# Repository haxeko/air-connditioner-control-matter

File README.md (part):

# Bộ điều khiển máy lạnh IR – Matter Thermostat (ESP32-S3)

Firmware ESP-IDF thuần (không Arduino, không ESPHome, không Home Assistant/MQTT/RainMaker/cloud) cho
ESP32-S3 N16R8:

- xuất hiện trong Google Home, Apple Home, SmartThings, Alexa, Aqara Home, Home Assistant… dưới dạng
  **máy lạnh / Matter Thermostat** tên **`May lanh IR v1.7.0`** (Tắt/Làm lạnh, Sưởi/Khô/Quạt khi profile máy
  lạnh có các chế độ đó; tốc độ quạt và đảo gió qua cluster Fan Control);
- tự tạo **fabric riêng (Fabric B)** để ghép cảm biến nhiệt độ Matter đã có trong nhà bằng Multi-Admin,
  rồi **subscribe** trực tiếp nhiệt độ của cảm biến (kể cả cảm biến Thread qua Border Router sẵn có);
- điều khiển máy lạnh bằng hồng ngoại (RMT native của ESP-IDF): **bấm remote một lần để tự nhận diện giao
  thức** (thư viện IRremoteESP8266, hơn 80 giao thức máy lạnh) rồi firmware tự tạo mọi lệnh, hoặc **học từng
  lệnh từ remote gốc** cho máy không có trong thư viện;
- **vẫn dùng remote gốc được**: mắt thu luôn nghe, bấm remote thì trạng thái mới (bật/tắt, chế độ, nhiệt độ,
  quạt, đảo gió) hiện lên Apple Home/Google Home… và lệnh sau từ ứng dụng nối tiếp đúng trạng thái đó;
- **nhấn BOOT 2 lần** để vào **chế độ ghép Matter** (LED RGB nháy xanh dương): ứng dụng nhà tìm thấy
  thiết bị **qua Bluetooth** (và qua Wi-Fi nhà nếu ESP đã vào mạng), thêm bằng **mã QR hoặc mã 11 số**;
  ứng dụng tự gửi Wi-Fi nhà cho ESP qua Bluetooth;
- **nhấn BOOT 3 lần** để mở Wi-Fi cấu hình và trang web tiếng Việt tại `http://192.168.4.1`;
- **giữ BOOT 10 giây rồi thả** để rời khỏi mọi ứng dụng nhà (giữ Wi-Fi, cảm biến, profile); **giữ 20 giây** để
  đặt lại gốc; cả hai cũng làm được trên web;
- **cập nhật firmware ngay trên trang web** (tải file `.bin`), không cần dây nạp; firmware mới lỗi thì tự quay
  về bản cũ;
- **tự phục hồi và tự báo lỗi**: treo thì watchdog khởi động lại; lỗi nghiêm trọng để lại báo cáo (tác vụ, vị trí)
  đọc được trên trang Chẩn đoán;
- lưu mọi cấu hình vào flash: mất điện không phải thiết lập lại;
- mọi tên thiết bị phát ra đều có **hậu tố phiên bản firmware** (`v1.7.0`): tên Matter, tên Bluetooth
  `AC-XXXX-v1.7.0`, Wi-Fi cấu hình `AC-Matter-XXXX-v1.7.0` – nhìn tên là biết thiết bị đang chạy bản nào.

### Có gì mới trong v1.7.0

Sửa đồng bộ với **Apple Home** (báo lỗi: bấm remote gốc thì mắt nhận nhưng Apple Home không đổi; bật trên Apple
Home thì một lúc sau tự tắt). Apple Home hiển thị thiết bị loại *Room Air Conditioner* như một máy sưởi/làm mát
(HomeKit Heater/Cooler, theo trả lời của kỹ sư Apple trên diễn đàn nhà phát triển); trạng thái “đang chạy” và quạt
của loại này lấy từ các thuộc tính mà bản trước không báo đúng:

- **Trạng thái đang chạy** (`ThermostatRunningState`, mới): Làm lạnh/Khô → “đang làm lạnh”, Sưởi → “đang sưởi”,
  Quạt → “quạt chạy”, Tắt → không. Trước đây thuộc tính này không có, nên Apple Home có thể hiện ô máy lạnh là
  Tắt/Chờ dù máy đang chạy – cả khi bật từ Apple Home lẫn khi bật bằng remote gốc.
- **Quạt Tự động không còn báo tốc độ hiện tại 0 %**: khi máy chạy với quạt tự động, tốc độ hiện tại báo là mức
  giữa (ví dụ 2/3). Ứng dụng nhà coi quạt 0 % là quạt tắt, tức máy tắt.
- **Quạt không còn bật/tắt máy lạnh**: trước đây ghi “quạt Off”/0 % (thanh trượt về cuối, hoặc ứng dụng tự ghi lại
  một tốc độ nó không biết) **tắt máy lạnh**, và chọn tốc độ khi máy tắt thì **bật máy**. Nay bật/tắt chỉ đi qua
  On/Off và chế độ (`SystemMode`); quạt Off/0 % nghĩa là quạt tự động; chọn tốc độ lúc máy tắt được dùng ở lần bật
  sau. Đây là nguyên nhân khả dĩ của “bật lên một lúc thì tự tắt” khi ứng dụng gửi kèm lệnh quạt.
- Trang **Máy lạnh** có dòng mới **Ứng dụng nhà đang thấy**: đúng những gì thiết bị đang báo qua Matter (bật/tắt,
  chế độ, nhiệt độ đặt, đang làm lạnh, quạt) và ai đổi lần cuối (ứng dụng nhà, remote gốc, trang này). Bấm remote
  rồi xem dòng này: nếu nó đổi mà Apple Home không đổi thì phần còn lại nằm ở Apple Home/bộ trung tâm.

Về chế độ: Apple Home chỉ có **Tắt / Sưởi / Làm lạnh / Tự động** cho máy lạnh, và chỉ hiện chế độ mà thiết bị khai báo
được (máy chỉ làm lạnh → chỉ Tắt và Làm lạnh). **Khô và Quạt không có trong Apple Home** (HomeKit không có hai chế độ
này); **Tự động** của Matter đòi máy có cả Sưởi, và với loại Room Air Conditioner thì Apple Home đang gửi Làm lạnh
khi chọn Tự động (lỗi Apple đã xác nhận). Khô/Quạt/Tự động vẫn dùng được bằng remote gốc, trang web, và ứng dụng hỗ
trợ (Home Assistant, SmartThings…). Xem [mục 10](#10-giới-hạn-đã-biết).

### Có gì mới trong v1.6.0

Bản rà soát và tối ưu (firmware và [mạch in v1.4](hardware/ac-ir-s3/README.md)). Cách điều khiển máy lạnh không
đổi; thiết bị tự phục hồi tốt hơn và nói được vì sao nó khởi động lại.

Độ tin cậy và chẩn đoán:

- **Treo thì tự khởi động lại**: một tác vụ chiếm CPU quá 15 giây làm thiết bị panic và khởi động lại (trước đây
  watchdog chỉ in cảnh báo ra cổng serial, thiết bị vẫn treo).
- **Báo cáo sự cố**: khi firmware lỗi nghiêm trọng (exception, abort, watchdog), thiết bị lưu core dump vào phân
  vùng `coredump` trước khi khởi động lại. Tab **Chẩn đoán → Sự cố khởi động lại** (và lệnh console `diag`) hiện
  tác vụ gây lỗi, vị trí và chuỗi địa chỉ gọi hàm – chỉ là địa chỉ trong chương trình, không có nội dung bộ nhớ.
  `python tools/decode_backtrace.py <địa chỉ…>` đổi các địa chỉ đó thành tên hàm bằng file
  `ac_matter_ir_vX.Y.Z_symbols.txt.gz` của đúng phiên bản (không cần ESP-IDF). Phân vùng này chỉ có trên bo nạp file `full` từ
  v1.6.0, hoặc nạp thêm file bảng phân vùng (xem [firmware/README.md](firmware/README.md)); bo chỉ cập nhật file
  app thì chạy bình thường, chỉ là không lưu báo cáo.
- **Ngăn xếp của từng tác vụ** (số byte còn trống ít nhất từ lúc khởi động) trên trang Chẩn đoán và lệnh `diag`:
  thấy ngay tác vụ nào sát giới hạn khi chạy trên bo thật.
- **Identify**: ứng dụng nhà bấm “nhận diện thiết bị” thì LED nháy **trắng**.

Sửa lỗi (các mục còn lại của lần rà soát trước):

- Phát IR bị quá hạn: kênh phát được dừng trước khi bộ đệm lệnh bị giải phóng (trước đây ngắt phát có thể còn đọc
  vùng nhớ đã trả lại).
- Vừa phát một lệnh, người dùng bấm remote gốc đổi trạng thái, rồi ứng dụng nhà lại yêu cầu đúng lệnh vừa phát
  (trong 1,5 giây): lệnh không còn bị coi là trùng và bỏ qua.
- Khởi động lại từ trang web (kể cả sau khi cập nhật firmware): lệnh IR đang chờ được phát nốt và trạng thái máy
  lạnh được lưu trước khi khởi động lại (trước đây có thể mất thay đổi của 10 giây cuối).
- Thuộc tính `ControlSequenceOfOperation` không còn ghi được sang kiểu mà máy lạnh không có (ví dụ “có sưởi” với
  profile chỉ làm lạnh); giá trị cũ sai được sửa lúc khởi động.
- Cổng cấu hình khởi tạo lỗi không còn làm thiết bị khởi động lại liên tục: thermostat và IR vẫn chạy.

Cấu hình:

- Tắt hẳn bộ mã ghép thử nghiệm của SDK (`CONFIG_ENABLE_TEST_SETUP_PARAMS=n`): không còn đường nào quay về
  passcode `20202021` (thiết bị vốn dùng mã riêng từng máy).
- Chọn GPIO không dùng được trên N16R8 (flash/PSRAM 26–37, UART0 43/44, chân strapping cho ngõ ra IR, hai chức
  năng trùng chân) bị từ chối **lúc build** thay vì hỏng lúc chạy.

### Có gì mới trong v1.5.0

Tính năng mới:

- **Cập nhật firmware qua web** (tab Chẩn đoán → *Cập nhật firmware*): chọn file `ac_matter_ir_vX.Y.Z_app_0x40000.bin`,
  thiết bị ghi vào khe OTA còn lại, kiểm tra nội dung rồi khởi động lại. Mọi dữ liệu được giữ. Firmware mới chạy
  thử 60 giây; nếu thiết bị reset trong thời gian đó, bootloader quay về bản cũ. Chi tiết ở [mục 7.5](#75-cập-nhật-firmware-và-đặt-lại).
- **Rời khỏi ứng dụng nhà ngay trên thiết bị**: gỡ từng hệ sinh thái hoặc tất cả (tab Nhà thông minh), hoặc
  **giữ BOOT 10 giây rồi thả** (LED nháy đỏ nhanh). Dùng khi hub đã mất hoặc đã xóa thiết bị lúc ESP mất mạng.
  Wi-Fi, cảm biến, profile IR và cài đặt được giữ; chế độ ghép tự bật lại.
- **Đặt lại gốc**: tab Chẩn đoán → *Đặt lại gốc*, hoặc **giữ BOOT 20 giây** (LED đỏ sáng liên tục). Xóa Wi-Fi, mọi
  fabric, cảm biến và cài đặt; giữ mã ghép Matter (tem QR đã in vẫn dùng được) và profile IR.

Sửa lỗi (tìm thấy khi rà soát mã nguồn):

- **Không còn tự phát lệnh IR**: trước đây, sau khi lưu/khóa/chọn profile (hoặc sau khi NVS bị xóa), thiết bị tự
  phát trạng thái thermostat trong vòng 30 giây – thường là lệnh *Tắt* – dù không ai yêu cầu. Nay khi chưa biết
  máy lạnh đang ở trạng thái nào, thiết bị coi như đã khớp và chỉ phát khi có thay đổi thật. Lúc khởi động cũng
  không bao giờ phát (trừ khi bật *Gửi lại trạng thái cuối sau khi mất điện*).
- **Bật máy kèm đổi chế độ** từ ứng dụng nhà (lệnh On và ghi SystemMode đi sát nhau) không còn có thể bị ghi đè
  bằng chế độ của lần bật trước.
- Ứng dụng nhà ghi lại đúng giá trị đang có (cảnh/tự động hóa lặp lại) không còn làm lùi chu kỳ bù theo cảm biến.
- Đổi Wi-Fi mà mất điện giữa lúc thử kết nối: lần khởi động sau tự quay về mạng cũ.
- Bộ thu IR: loại bỏ một tình huống tranh chấp hiếm giữa ngắt thu và việc dừng bộ thu (có thể gây khởi động lại).

### Có gì mới trong v1.4.0

- **Đồng bộ khi bấm remote gốc**: v1.3.0 chỉ dùng mắt thu lúc học/nhận diện, nên bấm remote thì máy lạnh đổi
  nhưng ESP và ứng dụng nhà không biết. Từ v1.4.0, khi profile đang dùng **đã khóa**, mắt thu nghe liên tục:
  lệnh của remote được giải mã theo profile (profile thư viện: đúng giao thức, ví dụ `SHARP_AC`; profile học
  thủ công: so với các lệnh đã học), rồi trạng thái mới được hiển thị trong ứng dụng nhà (SystemMode,
  nhiệt độ đặt, On/Off, quạt, đảo gió) **mà không phát lại IR**. Lệnh tiếp theo từ ứng dụng dùng trạng thái
  đó làm trạng thái trước (quan trọng với giao thức “đảo trạng thái” như Sharp). Chi tiết ở
  [mục 7.4](#74-ir), tắt được ở tab Thuật toán (*Đồng bộ khi bấm remote gốc*).
- Trang Máy lạnh có dòng **Remote gốc**: trạng thái remote đặt lần cuối, hoặc lý do lệnh cuối bị bỏ qua (ví dụ
  `giao thức NEC, profile dùng SHARP_AC` khi bấm remote TV). Lệnh `status` có dòng `Remote  :`.
- Thêm kiểm tra trên máy tính: chuỗi bấm remote Sharp (bật, đổi nhiệt độ, quạt, Sưởi, Khô, Tắt) qua mô phỏng
  mắt thu được đọc lại đúng trạng thái; trạng thái remote → trạng thái thermostat; sau khi bấm remote thuật
  toán không phát lại lệnh (cả chế độ Theo cảm biến ngoài).

### Có gì mới trong v1.3.0

- **Nhận diện remote tự động**: tab Máy lạnh → *Bắt đầu nhận diện* → bấm một nút trên remote. Firmware giải
  mã tín hiệu bằng thư viện **IRremoteESP8266 v2.9.0** (ESP-IDF thuần, không Arduino; `components/irremote_esp8266`),
  cho biết giao thức (Daikin, Panasonic, LG, Samsung, Mitsubishi, Toshiba, Gree, Midea, Fujitsu, Sharp,
  Hitachi, Haier, Coolix…), model và trạng thái đọc được. Phát thử vài lệnh do firmware **tự tạo**, đúng thì
  *Lưu và dùng*: một **profile thư viện** tạo được mọi tổ hợp chế độ × nhiệt độ × tốc độ quạt × đảo gió, không
  phải học từng lệnh. Không nhận ra thì vẫn học từng lệnh như trước. Chi tiết ở [mục 7.4](#74-ir).
- Sửa một lỗi của thư viện gốc (lệnh Kelon luôn bị gửi ở chế độ Sưởi), ghi trong
  `components/irremote_esp8266/README.md`.
- Thêm 1 538 kiểm tra trên máy tính: lệnh của 28 giao thức máy lạnh được tạo ra, mô phỏng méo tín hiệu của mắt
  thu, rồi nhận diện lại đúng giao thức và trạng thái.

### Có gì mới trong v1.2.0

- **Chỉnh quạt và đảo gió từ ứng dụng nhà**: thiết bị là **Room Air Conditioner** (kèm loại Thermostat) với
  cluster **Fan Control** (tốc độ theo các mức quạt đã học, Auto, đảo gió lên/xuống) và **On/Off**. Chi tiết ở
  [mục 7.1](#71-matter-thermostat-server-fabric-a). Tên thiết bị: `May lanh IR v1.2.0`.

### Có gì mới trong v1.1.0

- **Sửa lỗi “LED nháy xanh dương nhưng ứng dụng không thấy thiết bị”**: bản v1.0.0 không có Bluetooth,
  chỉ quảng bá trên mạng IP (DNS-SD). Ứng dụng Matter tìm thiết bị mới chủ yếu qua Bluetooth, còn đường IP
  chỉ chạy khi ESP đã vào đúng Wi-Fi nhà, điện thoại cùng mạng 2.4 GHz/không bị cách ly, và người dùng
  quét mã. v1.1.0 bật **CHIPoBLE** (NimBLE): trong chế độ ghép ESP quảng bá đồng thời qua Bluetooth và
  DNS-SD, QR có cờ BLE + mạng, BOOT x2 hoạt động cả khi ESP chưa có Wi-Fi (ứng dụng gửi Wi-Fi qua
  Bluetooth). Quan trọng: esp-matter mặc định tắt hẳn Bluetooth khi bảng fabric không rỗng
  (`CONFIG_USE_BLE_ONLY_FOR_COMMISSIONING`), mà Fabric B riêng của ESP luôn có mặt – nên tùy chọn này
  được tắt, nếu không Bluetooth sẽ bị gỡ ngay khi khởi động.
- **Đặt lại tên thiết bị có hậu tố phiên bản**: ProductName/NodeLabel/DNS-SD `DN` = `May lanh IR v1.1.0`,
  VendorName `DIY` (v1.0.0 phát ra `TEST_PRODUCT`/`TEST_VENDOR` mặc định của SDK và NodeLabel trống), tên
  Bluetooth `AC-XXXX-v1.1.0`, SSID cấu hình `AC-Matter-XXXX-v1.1.0`. Khi khởi động, NodeLabel trống hoặc còn
  tên mặc định của bản cũ được đặt thành tên mới; tên đã đổi trong ứng dụng nhà được giữ nguyên.
- Quảng bá DNS-SD có thêm `DT=769` (Thermostat). SoftwareVersion Matter = 10100.
- Mã số 11 chữ số không đổi; nội dung QR đổi (thêm cờ Bluetooth) – tem QR in từ v1.0.0 vẫn dùng được
  qua mạng Wi-Fi nhà, in lại tem để ứng dụng tìm qua Bluetooth.

> Trạng thái: toàn bộ mã nguồn đã viết và **build thành công** cho ESP32-S3; logic thuần đã có
> unit test chạy trên máy tính; giao diện web đã được kiểm thử tự động trong trình duyệt. Các phần cần
> phần cứng thật (Matter với hub, cảm biến, IR, nút bấm) **chưa được chạy trên thiết bị** – xem
> [mục 9](#9-đã-build-đã-thử-và-cần-phần-cứng-để-xác-nhận).

---

## Mục lục

1. [Kiến trúc](#1-kiến-trúc)
2. [Phiên bản SDK đã khóa](#2-phiên-bản-sdk-đã-khóa)
3. [Server + commissioner trên một CHIP stack: giới hạn SDK và giải pháp](#3-server--commissioner-trên-một-chip-stack-giới-hạn-sdk-và-giải-pháp)
4. [Phần cứng và đấu nối](#4-phần-cứng-và-đấu-nối)
5. [Build, nạp và xem log trên Windows (ESP-IDF Terminal)](#5-build-nạp-và-xem-log-trên-windows-esp-idf-terminal)
6. [Thiết lập từng bước](#6-thiết-lập-từng-bước)
7. [Hoạt động chi tiết](#7-hoạt-động-chi-tiết)
8. [Bảo mật](#8-bảo-mật)
9. [Đã build, đã thử và cần phần cứng để xác nhận](#9-đã-build-đã-thử-và-cần-phần-cứng-để-xác-nhận)
10. [Giới hạn đã biết](#10-giới-hạn-đã-biết)
11. [Cấu hình Kconfig](#11-cấu-hình-kconfig)
12. [Cấu trúc mã nguồn](#12-cấu-trúc-mã-nguồn)

---

## 1. Kiến trúc

```mermaid
flowchart LR
    subgraph Home["Hệ sinh thái nhà (Fabric A)"]
        HUB["Google Home / Apple Home / SmartThings<br/>(hub, Thread Border Router)"]
        PHONE["Điện thoại (ứng dụng nhà)<br/>tìm qua Bluetooth hoặc DNS-SD"]
    end
    SENSOR["Cảm biến nhiệt độ Matter<br/>(Wi-Fi hoặc Thread)<br/>ở Fabric A và Fabric B"]

    subgraph ESP["ESP32-S3 – một CHIP stack duy nhất"]
        direction TB
        SRV["matter_thermostat<br/>chip::Server, UDP 5540<br/>endpoint Thermostat 0x0301"]
        CMR["matter_commissioner<br/>DeviceControllerFactory + DeviceCommissioner<br/>UDP 5542, Fabric B do ESP sở hữu"]
        FT[("FabricTable + NVS<br/>dùng chung")]
        RT["remote_temperature<br/>subscribe 0x0402/0x0000<br/>stale timeout, backoff"]
        CC["climate_control<br/>Direct / bù theo cảm biến ngoài"]
        ACP["ac_profiles<br/>lệnh full-state đã học"]
        IR["ir_transceiver<br/>RMT TX/RX"]
        WIFI["wifi_config<br/>STA + SoftAP (AP+STA)"]
        WEB["web_config<br/>esp_http_server, chỉ trên AP"]
        BTN["button_handler<br/>BOOT x2: ghép Matter / x3: cấu hình"]
    end

    PHONE -- "ghép: BLE (CHIPoBLE, gửi Wi-Fi nhà) hoặc DNS-SD _matterc" --> SRV
    HUB -- "setpoint, SystemMode (Fabric A)" --> SRV
    SRV -- "LocalTemperature (null khi không hợp lệ)" --> HUB
    CMR -- "commissioning Multi-Admin (on-network)" --> SENSOR
    SENSOR -- "báo cáo subscription (Fabric B, CASE)" --> RT
    SRV --- FT
    CMR --- FT
    RT --> CC
    RT --> SRV
    SRV --> CC
    CC --> ACP --> IR -- "IR 38 kHz" --> AC["Máy lạnh"]
    BTN --> WIFI --> WEB
    WEB -.-> CMR
    WEB -.-> RT
    WEB -.-> CC
    WEB -.-> ACP
    WEB -.-> IR
```

Luồng dữ liệu chính:

| Đường | Mô tả |
|---|---|
| Hub → Thermostat | `SystemMode`, `OccupiedCoolingSetpoint` (và `OccupiedHeatingSetpoint` nếu có Sưởi) ghi vào endpoint Thermostat. Giá trị ngoài giới hạn/chế độ chưa học bị từ chối ngay ở callback PRE_UPDATE. |
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
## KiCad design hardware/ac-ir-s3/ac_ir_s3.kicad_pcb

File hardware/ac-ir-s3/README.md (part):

# Mạch in module IR máy lạnh – ESP32-S3-WROOM-1-N16R8 (KiCad 9)

Bo 2 lớp **30 × 39 mm**, cấp nguồn 5 V bằng **USB-C (chỉ cấp nguồn)** hoặc **đầu PH2.0** (GND, 5V), chỉ có nút
**BOOT**, nạp firmware qua **6 pad ở mặt dưới** (EN, 3V3, TX, RX, GND, IO0). Có 2 LED phát IR và mắt thu IR, chạy thẳng
firmware `ac_matter_ir` (cùng file `.bin` với bo DevKitC, không phải đổi cấu hình). Linh kiện dán từ **0603** trở
lên, pad loại hàn tay; riêng LED trạng thái D4 là WS2812B-2020 (2 × 2 mm, pad nằm dưới thân), nên hàn bằng khò
hoặc đặt xưởng hàn sẵn. Kể cả ăng-ten module chìa ra mép trên và đầu LED IR chìa ra mép dưới, cả cụm khoảng
31 × 49 mm.

**v1.4** (so với v1.3) – rà soát và tối ưu, firmware không đổi, cùng kích thước và vị trí cổng/LED:

| Thay đổi | Lý do |
|---|---|
| Lỗ via tản nhiệt dưới pad GND của module: 0,2 → **0,3 mm** (footprint riêng trong `ac_ir_s3.pretty`) | Bo 2 lớp giá rẻ (ví dụ JLCPCB) chỉ nhận lỗ via từ 0,3 mm. Lỗ nhỏ nhất trên bo giờ là 0,3 mm |
| **Via nối GND hai mặt** (68 via: lưới 3 mm, kể cả dưới module, cộng via cho từng mảng đồng bị cô lập) | Ở v1.3 các đường mặt dưới (+3V3, UART) cắt mặt GND thành mảng không nối được nên bị bỏ trống dưới module. Giờ mặt GND dưới liền, dòng hồi về đổi lớp ngay cạnh đường cắt |
| Bỏ **R2** (10 kΩ kéo lên GPIO0) | Chip tự kéo lên GPIO0 (khoảng 45 kΩ, mặc định lúc reset; sơ đồ mẫu của Espressif cũng không có điện trở này). Bỏ được đường +3V3 dài chạy ngang mặt dưới |
| Bỏ **C1** (1 µF ngõ ra LDO), **C3** 10 → **22 µF** | C3 nằm cách chân ra LDO 2,5 mm nên kiêm luôn tụ ngõ ra; 22 µF + 100 nF là giá trị datasheet module khuyên dùng cho xung dòng Wi-Fi |
| Thêm pad **EN** (TP6) cạnh pad 3V3 | Reset không cần rút điện (chập EN xuống GND), hoặc nối RTS của bộ chuyển để esptool tự reset. 5 pad cũ giữ nguyên vị trí |
| Pad GND nạp (TP4) có via riêng ngay cạnh, C2 nằm ngay dưới chân vào LDO, via GND của LDO nằm dưới thân | v1.3 nối pad GND bằng một đường 0,25 mm dài khoảng 13 mm; đường +3V3 ở mặt dưới giảm từ 44 mm xuống 22 mm |
| Kết quả đi dây lặp lại được | Chạy lại `gen/build.sh` cho đúng cùng một bo (trước đây thứ tự linh kiện phụ thuộc UUID ngẫu nhiên) |

Bớt 2 linh kiện phải hàn (R2, C1). Bản v1.4 **chưa được sản xuất hay đo thử**; bo v1.3 đã làm vẫn
dùng bình thường với cùng firmware.

**v1.3** (so với v1.2): LED trạng thái D4 đổi từ SK6812MINI (3,5 × 3,5 mm) sang **WS2812B-2020** (2 × 2 mm, LCSC
C965555), cùng giao thức và cùng chân nối, firmware không đổi.

**v1.2** (so với v1.1): bỏ header J2 cũ (UART + SDA/SCL), thay bằng 5 pad nạp ở mặt dưới; thêm đầu PH2.0 5 V;
mỗi nguồn vào đi qua một diode Schottky B5819W; bỏ 2 lỗ bắt vít; R8 còn 18 Ω (bù sụt áp diode); bo nhỏ từ
34 × 44 mm xuống 30 × 39 mm.

| File | Nội dung |
|---|---|
| `ac_ir_s3.kicad_pro` / `.kicad_sch` / `.kicad_pcb` | Dự án KiCad 9 (mở bằng KiCad 9.0 trở lên) |
| `fab/ac_ir_s3_v1.4_gerbers.zip` | Gerber + file khoan, gửi cho xưởng mạch in |
| `fab/ac_ir_s3_v1.4_bom.csv` | Danh sách linh kiện (giá trị, thông số, mã hãng, mã LCSC) |
| `fab/ac_ir_s3_v1.4_cpl.csv` | Tọa độ đặt linh kiện (nếu đặt xưởng hàn SMT), gốc ở góc dưới-trái bo |
| `docs/ac_ir_s3_v1.4_schematic.pdf` / `.png` | Sơ đồ nguyên lý |
| `docs/ac_ir_s3_v1.4_assembly_top.pdf` | Bản vẽ lắp ráp: vị trí và tên từng linh kiện |
| `docs/ac_ir_s3_v1.4_top.png`, `_bottom.png` | Ảnh mặt trên / mặt dưới bo |
| `docs/ac_ir_s3_v1.4_erc.txt`, `_drc.txt` | Kết quả kiểm tra ERC / DRC |
| `ac_ir_s3.pretty/`, `fp-lib-table` | Thư viện footprint của dự án: module với via tản nhiệt 0,3 mm |
| `gen/` | Script đã sinh ra sơ đồ, bo, đường mạch và các file trên |

## Kiểm tra thiết kế

- **ERC**: 0 lỗi, 0 cảnh báo.
- **DRC** (kèm so khớp sơ đồ – mạch in): 0 vi phạm, 0 chân chưa nối, 0 lệch giữa sơ đồ và bo.
- Luật thiết kế: khoảng hở 0,2 mm; đường tín hiệu 0,25 mm, nguồn 0,5 mm; via 0,6/0,3 mm (nguồn 0,8/0,4 mm); đồng
  cách mép bo 0,3 mm; cổ hẹp nhỏ nhất của mặt đồng GND 0,15 mm. Phủ đồng GND cả hai mặt, nối nhau bằng 84 via GND.
- Lỗ nhỏ nhất **0,3 mm** (104 lỗ via 0,3 mm, 13 lỗ 0,4 mm), nằm trong mức tối thiểu JLCPCB công bố cho bo 1–2
  lớp. Via được phủ sơn (tented), kể cả các via GND nằm dưới module.
- Còn một mảng đồng GND khoảng 2 mm² ở mặt dưới cạnh pad EN không có chỗ đặt via nên để trống (không ảnh hưởng).
- Bỏ qua cảnh báo "chữ in bị mép bo cắt": ăng-ten module, cổng USB-C và LED/mắt thu IR cố ý chìa ra ngoài mép,
  phần chữ in của chúng nằm ngoài bo thì không in.

## Mạch

| Khối | Linh kiện | Ghi chú |
|---|---|---|
| Nguồn vào | J1 USB-C 6 chân chỉ cấp nguồn (GCT USB4125-GF-A) + R3/R4 5,1 kΩ (CC); J2 PH2.0 2 chân (1 = GND, 2 = 5V); D5, D6 Schottky B5819W; F1 PTC 0,75 A | Dùng nguồn nào cũng được, cắm cả hai cùng lúc cũng không sao; cắm ngược cực PH2.0 thì diode chặn, không hỏng |
| 3,3 V | U2 AP2112K-3.3 (600 mA), C2 4,7 µF ở ngõ vào, C3 22 µF + C4 100 nF sát chân 3V3 module (C3 kiêm tụ ngõ ra LDO) | LDO tỏa khoảng (4,6 − 3,3) V × dòng, ước tính 0,1–0,2 W trung bình: ấm nhẹ là bình thường |
| ESP32-S3 | U1 ESP32-S3-WROOM-1-**N16R8**, R1 10 kΩ + C5 1 µF ở EN (tự reset khi cấp điện) | GPIO0 do chip tự kéo lên; GPIO35–37 bỏ trống (PSRAM octal); GPIO8/9/19/20 không dùng |
| Phát IR | D2, D3: 2 LED IR 5 mm 940 nm **nối tiếp**, R8 18 Ω 1206, Q1 AO3400A, R6 100 Ω, R7 10 kΩ, C8 4,7 µF | (5 V − 0,4 V − 2 × 1,35 V) / 18 Ω ≈ 100 mA đỉnh, sóng mang 38 kHz 33 %. Cần xa hơn: R8 = 10 Ω 1206 (≈ 170 mA đỉnh, ≈ 55 mA trung bình trong lúc phát, vẫn dưới mức 100 mA liên tục của LED) |
| Thu IR | U4 TSOP38238 / VS1838B, lọc nguồn R5 100 Ω + C6 4,7 µF | Chân **OUT – GND – VS**, nguồn 3,3 V |
| LED trạng thái | D4 WS2812B-2020 ở GPIO48, cấp từ 5 V qua D1 1N4148W (≈ 3,9 V) | Ở 3,9 V LED cần mức cao ≥ 0,7 × 3,9 ≈ 2,7 V: mức 3,3 V của ESP đủ |
| Nút | SW1 **BOOT** (GPIO0) | BOOT 2 lần: ghép Matter; 3 lần: Wi-Fi cấu hình; giữ BOOT khi cấp điện: chế độ nạp |
| Pad nạp (mặt dưới) | TP6 EN · TP1 3V3 · TP2 TX · TP3 RX · TP4 GND · TP5 IO0, cách nhau 2,54 mm | UART0 nạp firmware, xem log, console; IO0 sát GND để chập khi nạp; EN không bắt buộc |

Chân khớp cấu hình mặc định của firmware: IR TX = GPIO4 (mức cao = LED sáng), IR RX = GPIO5 (tích cực mức
thấp), BOOT = GPIO0, LED RGB = GPIO48. Cảm biến nhiệt độ dây (SDA/SCL) không còn trên bo; firmware mặc định đã
không dùng nên không cần đổi gì.

Tiêu thụ: đỉnh khoảng 0,5 A (Wi-Fi phát ~350 mA + xung LED IR 100 mA). Nguồn 5 V (cốc sạc USB hoặc nguồn nối
vào PH2.0) nên từ 1 A trở lên.

## Bố trí

- **Ăng-ten** của module chìa ra ngoài mép trên của bo. Không đặt kim loại, dây điện hay bo mạch khác trong
  khoảng 15 mm quanh ăng-ten, không cho vào hộp kim loại.
- **USB-C** ở mép trái; **PH2.0** (loại đứng, cắm từ trên xuống) ở phía phải, chữ "5V" in cạnh chân 5 V.
- Mép dưới: **LED IR – mắt thu – LED IR**, cả ba nhìn ra ngoài cùng một hướng. Hướng mép này về phía máy lạnh;
  vỏ hộp cần cửa sổ trong suốt với hồng ngoại (hoặc khoét lỗ) trước LED và mắt thu.
- Nút BOOT ở mép phải. Pad nạp ở mặt dưới, ngay dưới module.
- Không có lỗ bắt vít (để bo nhỏ nhất): giữ bo bằng rãnh trong vỏ hộp, keo hoặc băng dính 2 mặt ở mặt dưới
  (chừa pad nạp).

## Lắp ráp

1. Hàn **D4 trước tiên bằng khò** (khoảng 300 °C, có kem hàn, không quá 10 giây; WS2812B-2020 chịu nhiệt kém,
   pad nằm hết dưới thân nên mỏ hàn không với tới). Đặt xưởng hàn SMT thì bỏ qua bước này.
   Sau đó hàn: U2, Q1, D1, D5, D6, các R/C, F1, nút BOOT, rồi J1 (6 chân bước khoảng 1 mm, hàn
   chắc 4 chân vỏ), cuối cùng module U1. Pad GND giữa module nên hàn bằng khò hoặc bếp hàn; hàn tay thì vẫn chạy
   vì module còn GND ở chân 1 và 40. J1 là GCT USB4125-GF-A; dùng loại USB-C 6 chân SMD khác thì so vị trí chân
   và chân vỏ với bản vẽ lắp ráp trước khi mua.
2. Chú ý chiều: vạch catốt của D1, D5, D6; chân 1 của D4 theo dấu chân 1 trên bản vẽ lắp ráp (đối chiếu dấu chân 1 trên thân LED với datasheet WS2812B-2020); U2/Q1 theo dấu chân 1 trên bản vẽ lắp ráp.
3. **LED IR**: chân dài (anốt) vào lỗ tròn, chân ngắn (catốt) vào lỗ vuông. Bẻ chân 90° cho LED nằm sát mặt
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
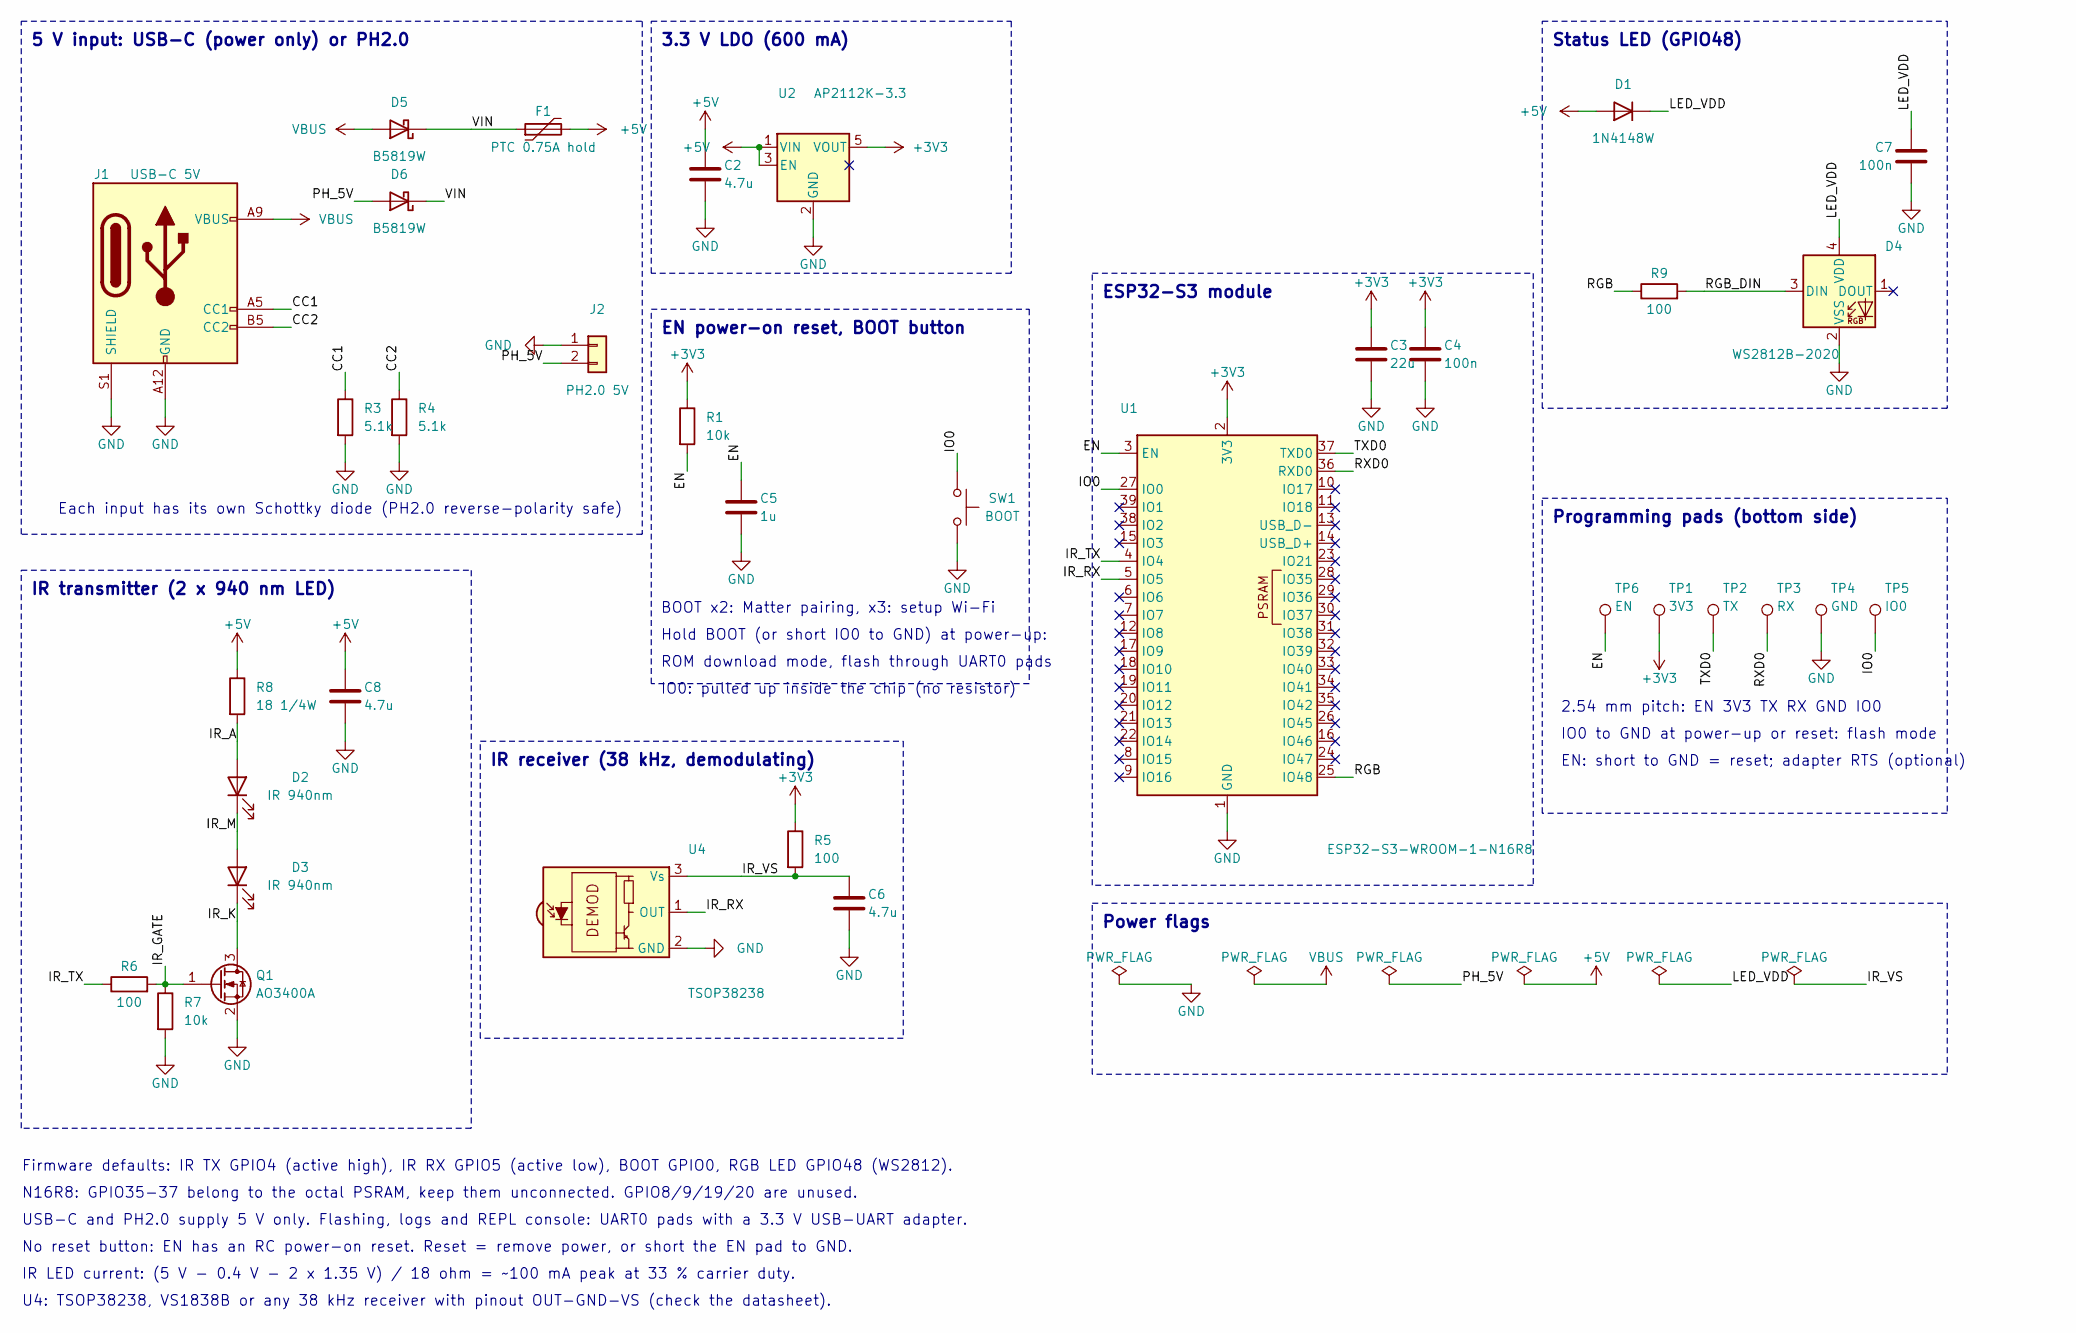
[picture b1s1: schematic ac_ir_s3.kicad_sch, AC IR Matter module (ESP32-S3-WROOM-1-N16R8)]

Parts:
C2, C6, C8: 4.7u; C_0805_2012Metric_Pad1.18x1.45mm_HandSolder; LCSC C1779
C3: 22u; C_0805_2012Metric_Pad1.18x1.45mm_HandSolder; LCSC C45783
C4, C7: 100n; C_0603_1608Metric_Pad1.08x0.95mm_HandSolder; LCSC C14663
C5: 1u; C_0603_1608Metric_Pad1.08x0.95mm_HandSolder; LCSC C15849
D1: 1N4148W; D_SOD-123; MPN 1N4148W; LCSC C81598
D2, D3: IR 940nm; LED_D5.0mm_Horizontal_O1.27mm_Z3.0mm_IRBlack; MPN TSAL6200
D4: WS2812B-2020; LED_WS2812B-2020_PLCC4_2.0x2.0mm; MPN WS2812B-2020; LCSC C965555
D5, D6: B5819W; D_SOD-123; MPN B5819W; LCSC C8598
F1: PTC 0.75A hold; Fuse_1206_3216Metric_Pad1.42x1.75mm_HandSolder
J1: USB-C 5V; USB_C_Receptacle_GCT_USB4125-xx-x_6P_TopMnt_Horizontal; MPN GCT USB4125-GF-A
J2: PH2.0 5V; JST_PH_B2B-PH-K_1x02_P2.00mm_Vertical; MPN JST B2B-PH-K-S
Q1: AO3400A; SOT-23; MPN AO3400A; LCSC C20917
R1, R7: 10k; R_0603_1608Metric_Pad0.98x0.95mm_HandSolder; LCSC C25804
R3, R4: 5.1k; R_0603_1608Metric_Pad0.98x0.95mm_HandSolder; LCSC C23186
R5, R6, R9: 100; R_0603_1608Metric_Pad0.98x0.95mm_HandSolder; LCSC C22775
R8: 18 1/4W; R_1206_3216Metric_Pad1.30x1.75mm_HandSolder
SW1: BOOT; SW_SPST_PTS810; MPN C&K PTS810 SJM 250 SMTR LFS
TP1: 3V3; TestPoint_Pad_1.5x1.5mm
TP2: TX; TestPoint_Pad_1.5x1.5mm
TP3: RX; TestPoint_Pad_1.5x1.5mm
TP4: GND; TestPoint_Pad_1.5x1.5mm
TP5: IO0; TestPoint_Pad_1.5x1.5mm
TP6: EN; TestPoint_Pad_1.5x1.5mm
U1: ESP32-S3-WROOM-1-N16R8; ESP32-S3-WROOM-1; MPN ESP32-S3-WROOM-1-N16R8
U2: AP2112K-3.3; SOT-23-5; MPN AP2112K-3.3TRG1; LCSC C51118
U4: TSOP38238; Vishay_MINICAST-3Pin; MPN TSOP38238

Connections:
+3V3: C3.1, C4.1, R1.1, R5.1, TP1.1, U1.2 (3V3), U2.5 (VOUT)
+5V: C2.1, C8.1, D1.2 (A), F1.2, R8.1, U2.1 (VIN), U2.3 (EN)
/CC1: J1.A5 (CC1), R3.1
/CC2: J1.B5 (CC2), R4.1
/EN: C5.1, R1.2, TP6.1, U1.3 (EN)
/IO0: SW1.1, TP5.1, U1.27 (IO0)
/IR_A: D2.2 (A), R8.2
/IR_GATE: Q1.1 (G), R6.2, R7.1
/IR_K: D3.1 (K), Q1.3 (D)
/IR_M: D2.1 (K), D3.2 (A)
/IR_RX: U1.5 (IO5), U4.1 (OUT)
/IR_TX: R6.1, U1.4 (IO4)
/IR_VS: C6.1, R5.2, U4.3 (Vs)
/LED_VDD: C7.1, D1.1 (K), D4.4 (VDD)
/PH_5V: D6.2 (A), J2.2
/RGB: R9.1, U1.25 (IO48)
/RGB_DIN: D4.3 (DIN), R9.2
/RXD0: TP3.1, U1.36 (RXD0)
/TXD0: TP2.1, U1.37 (TXD0)
/VIN: D5.1 (K), D6.1 (K), F1.1
GND: C2.2, C3.2, C4.2, C5.2, C6.2, C7.2, C8.2, D4.2 (VSS), J1.A12 (GND), J1.B12 (GND), J1.S1 (SHIELD), J2.1, Q1.2 (S), R3.2, R4.2, R7.2, SW1.2, TP4.1, U1.1 (GND), U1.40 (GND), U1.41 (GND), U2.2 (GND), U4.2 (GND)
VBUS: D5.2 (A), J1.A9 (VBUS), J1.B9 (VBUS)

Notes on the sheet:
5 V input: USB-C (power only) or PH2.0
3.3 V LDO (600 mA)
EN power-on reset, BOOT button
ESP32-S3 module
IR transmitter (2 x 940 nm LED)
IR receiver (38 kHz, demodulating)
Status LED (GPIO48)
Programming pads (bottom side)
Power flags
BOOT x2: Matter pairing, x3: setup Wi-Fi
Hold BOOT (or short IO0 to GND) at power-up:
ROM download mode, flash through UART0 pads
IO0: pulled up inside the chip (no resistor)
2.54 mm pitch: EN 3V3 TX RX GND IO0
IO0 to GND at power-up or reset: flash mode
EN: short to GND = reset; adapter RTS (optional)
Each input has its own Schottky diode (PH2.0 reverse-polarity safe)
Firmware defaults: IR TX GPIO4 (active high), IR RX GPIO5 (active low), BOOT GPIO0, RGB LED GPIO48 (WS2812).
N16R8: GPIO35-37 belong to the octal PSRAM, keep them unconnected. GPIO8/9/19/20 are unused.
USB-C and PH2.0 supply 5 V only. Flashing, logs and REPL console: UART0 pads with a 3.3 V USB-UART adapter.
No reset button: EN has an RC power-on reset. Reset = remove power, or short the EN pad to GND.
IR LED current: (5 V - 0.4 V - 2 x 1.35 V) / 18 ohm = ~100 mA peak at 33 % carrier duty.
U4: TSOP38238, VS1838B or any 38 kHz receiver with pinout OUT-GND-VS (check the datasheet).

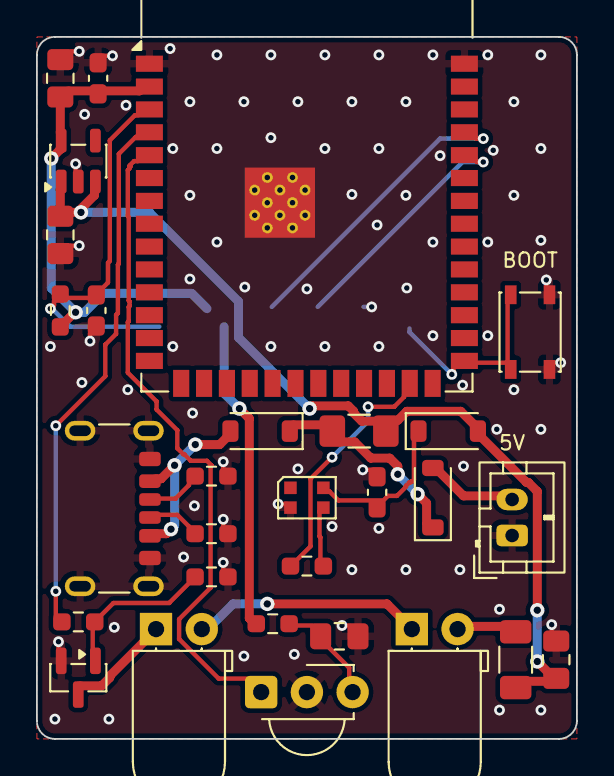
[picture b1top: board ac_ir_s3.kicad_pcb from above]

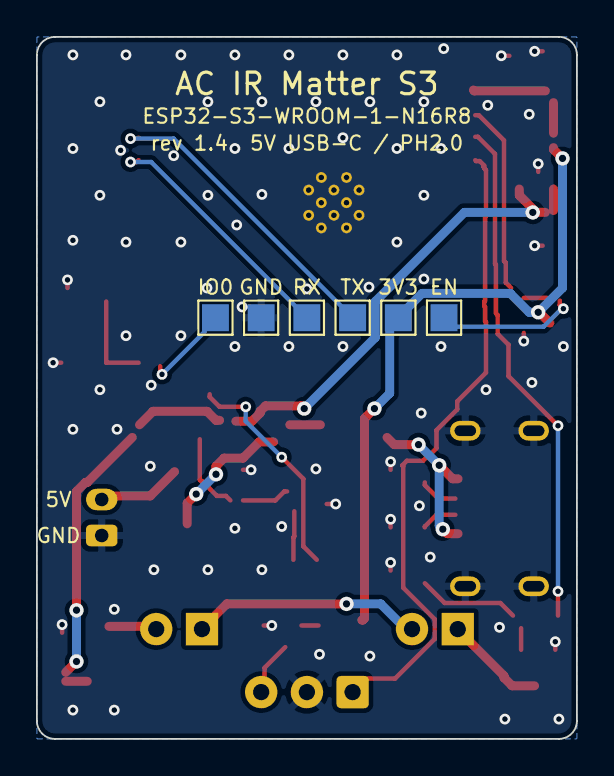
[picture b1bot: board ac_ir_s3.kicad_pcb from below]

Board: 2 copper layers, 30.0 x 39.0 mm, 35 parts (6 on the bottom side), 22 nets.

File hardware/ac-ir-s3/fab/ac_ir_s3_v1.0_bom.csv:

"Designator","Value","Spec","Footprint","MPN","LCSC","Qty"
"C1,C5","1u","0603 X5R 25 V","Capacitor_SMD:C_0603_1608Metric_Pad1.08x0.95mm_HandSolder","","C15849","2"
"C2,C6,C8","4.7u","0805 X5R 25 V","Capacitor_SMD:C_0805_2012Metric_Pad1.18x1.45mm_HandSolder","","C1779","3"
"C3","10u","0805 X5R 25 V","Capacitor_SMD:C_0805_2012Metric_Pad1.18x1.45mm_HandSolder","","C15850","1"
"C4,C7","100n","0603 X7R 50 V","Capacitor_SMD:C_0603_1608Metric_Pad1.08x0.95mm_HandSolder","","C14663","2"
"D1","1N4148W","small-signal diode SOD-123","Diode_SMD:D_SOD-123","1N4148W","C81598","1"
"D2,D3","IR 940nm","IR LED 5 mm 940 nm, >= 100 mA","LED_THT:LED_D5.0mm_Horizontal_O1.27mm_Z3.0mm_IRBlack","TSAL6200","","2"
"D4","SK6812MINI","addressable RGB LED 3.5x3.5 mm","LED_SMD:LED_SK6812MINI_PLCC4_3.5x3.5mm_P1.75mm","SK6812MINI","","1"
"F1","PTC 0.75A hold","PTC resettable fuse 1206, I_hold 0.75 A, >= 6 V","Fuse:Fuse_1206_3216Metric_Pad1.42x1.75mm_HandSolder","","","1"
"J1","USB-C","USB-C receptacle 16P, SMD + 4 shell pins","Connector_USB:USB_C_Receptacle_HRO_TYPE-C-31-M-12","HRO TYPE-C-31-M-12","C165948","1"
"J2","UART0+I2C","male pin header 1x6 2.54 mm (optional)","Connector_PinHeader_2.54mm:PinHeader_1x06_P2.54mm_Vertical","","","1"
"Q1","AO3400A","N-MOSFET 30 V, logic level, SOT-23","Package_TO_SOT_SMD:SOT-23","AO3400A","C20917","1"
"R1,R2,R7","10k","0603 1%","Resistor_SMD:R_0603_1608Metric_Pad0.98x0.95mm_HandSolder","","C25804","3"
"R3,R4","5.1k","0603 1%","Resistor_SMD:R_0603_1608Metric_Pad0.98x0.95mm_HandSolder","","C23186","2"
"R5,R6,R9","100","0603 1%","Resistor_SMD:R_0603_1608Metric_Pad0.98x0.95mm_HandSolder","","C22775","3"
"R8","22 1/4W","1206 1% 0.25 W","Resistor_SMD:R_1206_3216Metric_Pad1.30x1.75mm_HandSolder","","","1"
"SW1","BOOT","tactile switch 4.2x3.2 mm SMD","Button_Switch_SMD:SW_SPST_PTS810","C&K PTS810 SJM 250 SMTR LFS","","1"
"SW2","RESET","tactile switch 4.2x3.2 mm SMD","Button_Switch_SMD:SW_SPST_PTS810","C&K PTS810 SJM 250 SMTR LFS","","1"
"U1","ESP32-S3-WROOM-1-N16R8","Wi-Fi/BLE module, 16 MB flash, 8 MB octal PSRAM","RF_Module:ESP32-S3-WROOM-1","ESP32-S3-WROOM-1-N16R8","","1"
"U2","AP2112K-3.3","LDO 3.3 V 600 mA SOT-23-5","Package_TO_SOT_SMD:SOT-23-5","AP2112K-3.3TRG1","C51118","1"
"U3","USBLC6-2SC6","USB ESD protection SOT-23-6","Package_TO_SOT_SMD:SOT-23-6","USBLC6-2SC6","C7519","1"
"U4","TSOP38238","IR receiver 38 kHz, pinout OUT-GND-VS (TSOP38238, VS1838B)","OptoDevice:Vishay_MINICAST-3Pin","TSOP38238","","1"

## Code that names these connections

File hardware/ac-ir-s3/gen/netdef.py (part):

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    # 5 V from either input through its own Schottky diode (either or both may be connected, PH2.0 is
    # reverse-polarity safe), then the PTC fuse.
    "J2": dict(lib="Connector_Generic:Conn_01x02", value="PH2.0 5V", fp="Connector_JST:JST_PH_B2B-PH-K_1x02_P2.00mm_Vertical",
               pins={"1": "GND", "2": "PH_5V"},
               fields={"Spec": "JST PH 2.0 mm 2-pin vertical, 1 = GND, 2 = +5 V", "MPN": "JST B2B-PH-K-S"}),
    "D5": dict(lib="Device:D_Schottky", value="B5819W", fp="Diode_SMD:D_SOD-123",
               pins={"2": "VBUS", "1": "VIN"},
               fields={"Spec": "Schottky 1 A 40 V SOD-123 (USB-C input)", "MPN": "B5819W", "LCSC": "C8598"}),
    "D6": dict(lib="Device:D_Schottky", value="B5819W", fp="Diode_SMD:D_SOD-123",
               pins={"2": "PH_5V", "1": "VIN"},
               fields={"Spec": "Schottky 1 A 40 V SOD-123 (PH2.0 input)", "MPN": "B5819W", "LCSC": "C8598"}),
    "F1": dict(lib="Device:Polyfuse", value="PTC 0.75A hold", fp="Fuse:Fuse_1206_3216Metric_Pad1.42x1.75mm_HandSolder",
               pins={"1": "VIN", "2": "+5V"}, fields={"Spec": "PTC resettable fuse 1206, I_hold 0.75 A, >= 6 V"}),
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               pins={"1": "+5V", "3": "+5V", "2": "GND", "5": "+3V3"},
               fields={"Spec": "LDO 3.3 V 600 mA SOT-23-5", "MPN": "AP2112K-3.3TRG1", "LCSC": "C51118"}),
    "Q1": dict(lib="Transistor_FET:AO3400A", value="AO3400A", fp="Package_TO_SOT_SMD:SOT-23",
               pins={"1": "IR_GATE", "2": "GND", "3": "IR_K"}, fields={"Spec": "N-MOSFET 30 V, logic level, SOT-23", "MPN": "AO3400A", "LCSC": "C20917"}),
    "D1": dict(lib="Diode:1N4148W", value="1N4148W", fp="Diode_SMD:D_SOD-123",
               pins={"1": "LED_VDD", "2": "+5V"}, fields={"Spec": "small-signal diode SOD-123", "MPN": "1N4148W", "LCSC": "C81598"}),
    "D2": dict(lib="Device:LED", value="IR 940nm", fp="LED_THT:LED_D5.0mm_Horizontal_O1.27mm_Z3.0mm_IRBlack",
               pins={"2": "IR_A", "1": "IR_M"}, fields={"Spec": "IR LED 5 mm 940 nm, >= 100 mA", "MPN": "TSAL6200"}),
    "D3": dict(lib="Device:LED", value="IR 940nm", fp="LED_THT:LED_D5.0mm_Horizontal_O1.27mm_Z3.0mm_IRBlack",
               pins={"2": "IR_M", "1": "IR_K"}, fields={"Spec": "IR LED 5 mm 940 nm, >= 100 mA", "MPN": "TSAL6200"}),
    "D4": dict(lib="LED:WS2812B-2020", value="WS2812B-2020", fp="LED_SMD:LED_WS2812B-2020_PLCC4_2.0x2.0mm",
               pins={"4": "LED_VDD", "2": "GND", "3": "RGB_DIN"},
               fields={"Spec": "addressable RGB LED 2.0x2.0 mm (reflow)", "MPN": "WS2812B-2020", "LCSC": "C965555"}),
    "U4": dict(lib="Interface_Optical:TSOP382xx", value="TSOP38238", fp="OptoDevice:Vishay_MINICAST-3Pin",
               pins={"1": "IR_RX", "2": "GND", "3": "IR_VS"},
               fields={"Spec": "IR receiver 38 kHz, pinout OUT-GND-VS (TSOP38238, VS1838B)", "MPN": "TSOP38238"}),
    "SW1": dict(lib="Switch:SW_Push", value="BOOT", fp="Button_Switch_SMD:SW_SPST_PTS810",
                pins={"1": "IO0", "2": "GND"}, fields={"Spec": "tactile switch 4.2x3.2 mm SMD", "MPN": "C&K PTS810 SJM 250 SMTR LFS"}),
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    # 45 kOhm), as in Espressif's module reference schematic, and the firmware enables the pull-up too.
    "R3": dict(lib="Device:R", value="5.1k", fp=R0603, spec="0603 1%", pins={"1": "CC1", "2": "GND"}, fields={"LCSC": "C23186"}),
    "R4": dict(lib="Device:R", value="5.1k", fp=R0603, spec="0603 1%", pins={"1": "CC2", "2": "GND"}, fields={"LCSC": "C23186"}),
    "R5": dict(lib="Device:R", value="100", fp=R0603, spec="0603 1%", pins={"1": "+3V3", "2": "IR_VS"}, fields={"LCSC": "C22775"}),
    "R6": dict(lib="Device:R", value="100", fp=R0603, spec="0603 1%", pins={"1": "IR_TX", "2": "IR_GATE"}, fields={"LCSC": "C22775"}),
    "R7": dict(lib="Device:R", value="10k", fp=R0603, spec="0603 1%", pins={"1": "IR_GATE", "2": "GND"}, fields={"LCSC": "C25804"}),
    "R8": dict(lib="Device:R", value="18 1/4W", fp=R1206, spec="1206 1% 0.25 W", pins={"1": "+5V", "2": "IR_A"},
               fields={}),
    "R9": dict(lib="Device:R", value="100", fp=R0603, spec="0603 1%", pins={"1": "RGB", "2": "RGB_DIN"}, fields={"LCSC": "C22775"}),
    "C2": dict(lib="Device:C", value="4.7u", fp=C0805, spec="0805 X5R 25 V", pins={"1": "+5V", "2": "GND"}, fields={"LCSC": "C1779"}),
    # 22 uF + 100 nF at the module supply pin, as in the ESP32-S3-WROOM-1 datasheet (Wi-Fi TX current bursts).
    # C3 sits 2.5 mm from the LDO output pin and is its output capacitor too (the AP2112K needs >= 1 uF).
    "C3": dict(lib="Device:C", value="22u", fp=C0805, spec="0805 X5R 25 V", pins={"1": "+3V3", "2": "GND"}, fields={"LCSC": "C45783"}),
    "C4": dict(lib="Device:C", value="100n", fp=C0603, spec="0603 X7R 50 V", pins={"1": "+3V3", "2": "GND"}, fields={"LCSC": "C14663"}),
    "C5": dict(lib="Device:C", value="1u", fp=C0603, spec="0603 X5R 25 V", pins={"1": "EN", "2": "GND"}, fields={"LCSC": "C15849"}),
    "C6": dict(lib="Device:C", value="4.7u", fp=C0805, spec="0805 X5R 25 V", pins={"1": "IR_VS", "2": "GND"}, fields={"LCSC": "C1779"}),
    "C7": dict(lib="Device:C", value="100n", fp=C0603, spec="0603 X7R 50 V", pins={"1": "LED_VDD", "2": "GND"}, fields={"LCSC": "C14663"}),
    "C8": dict(lib="Device:C", value="4.7u", fp=C0805, spec="0805 X5R 25 V", pins={"1": "+5V", "2": "GND"}, fields={"LCSC": "C1779"}),
}

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

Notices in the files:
README.md:
IRremoteESP8266 | **v2.9.0** (commit `a0c988c9af`, LGPL-2.1) | mã nguồn đi kèm trong `components/irremote_esp8266/` (một bản sửa lỗi, xem README của component)
irremote_esp8266/ IRremoteESP8266 v2.9.0 (LGPL-2.1) + port/ cho ESP-IDF không Arduino
